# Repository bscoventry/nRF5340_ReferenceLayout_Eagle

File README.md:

# nRF5340 Eagle Reference Layout

This is a recreation of Nordic's reference layout for the nRF5340 in Eagle. The layout given by Nordic is in Altium, and it might be useful to those who do not have access to that software. While it's pin and pcb perfect replication, users should use with caution and validation since I am not Nordic.

# Nordic nRF5340 Circuit Configuration 3.
This is implemented for the reference circuit configuration 3, which has the following configuration parameters:

This can be easily ajdusted to other configurations by minor changes to reference schematic and board layout.

Note: This does require a 4 layer board due to Eagle restrictions on microvias. Will fix this in later iterations.

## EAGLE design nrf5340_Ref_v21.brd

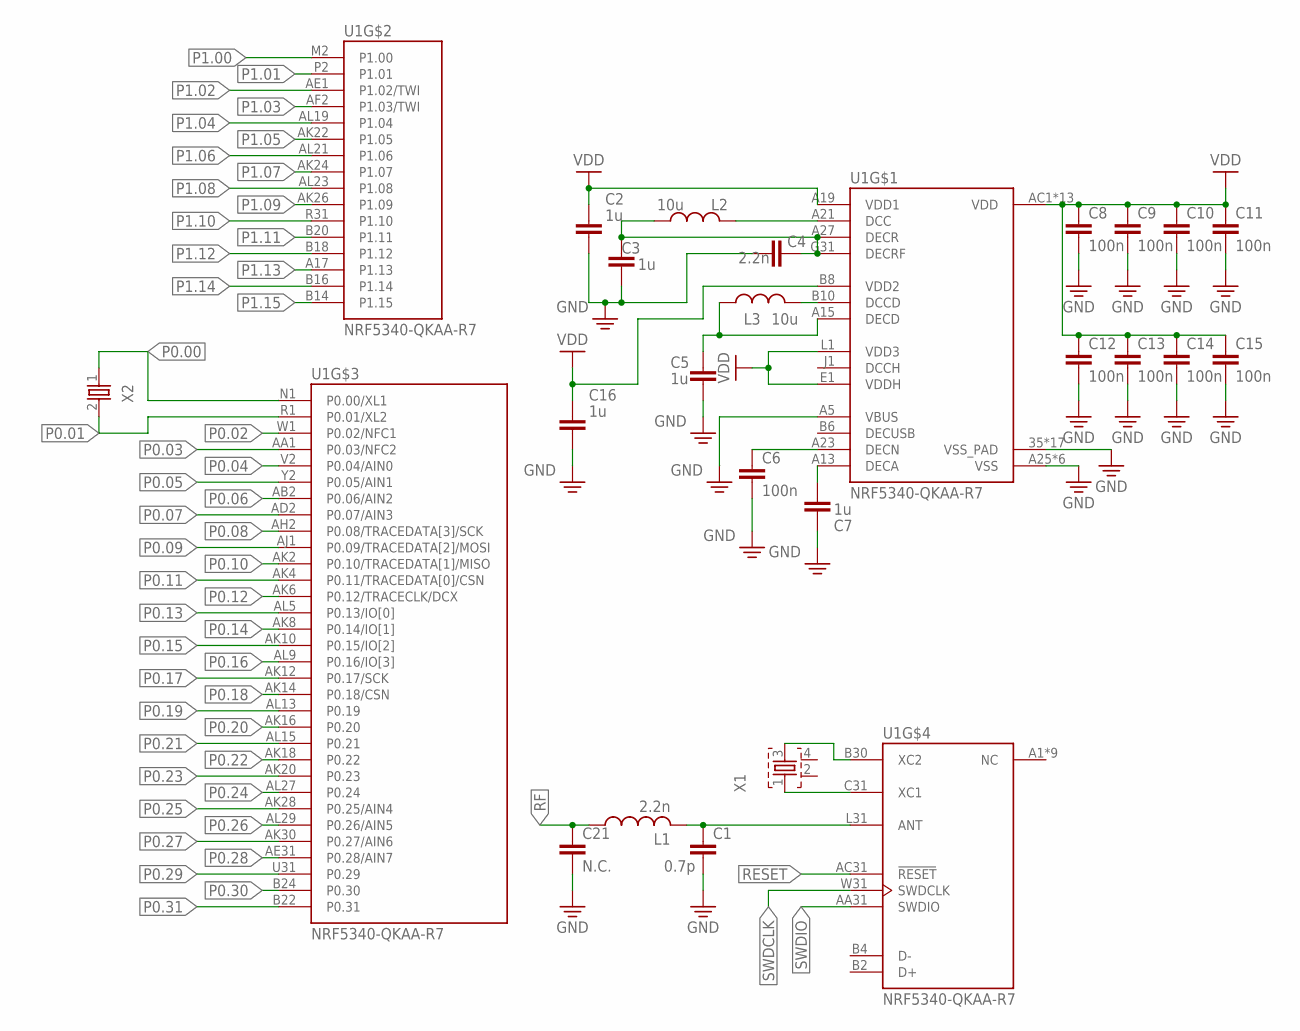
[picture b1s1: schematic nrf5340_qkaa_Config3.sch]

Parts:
C1: 0.7p; RESC0201_N
C2, C3, C5, C7, C16: 1u; CAPC1005X60
C4: 2.2n; RESC0201_N
C6, C8, C9, C10, C11, C12, C13, C14, C15: 100n; RESC0201_N
C21: N.C.; RESC0201_N
L1: 2.2n; RESC0201_N
L2, L3: 10u; INDC1608X95N
U1: NRF5340-QKAA-R7; XCVR_NRF5340-QKAA-R7
X1: XTAL_32MHZ; BT-XTAL_2016_N
X2: XTAL_32KHZ; XTAL_3215_N

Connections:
DCCH: U1.J1 (DCCH)
DECUSB: U1.B6 (DECUSB)
GND: C1.2, C2.2, C3.2, C4.2, C5.2, C6.2, C7.2, C8.2, C9.2, C10.2, C11.2, C12.2, C13.2, C14.2, C15.2, C16.2, C21.2, U1.35 (VSS_PAD), U1.36 (VSS_PAD), U1.37 (VSS_PAD), U1.38 (VSS_PAD), U1.39 (VSS_PAD), U1.40 (VSS_PAD), U1.41 (VSS_PAD), U1.43 (VSS_PAD), U1.44 (VSS_PAD), U1.45 (VSS_PAD), U1.46 (VSS_PAD), U1.47 (VSS_PAD), U1.48 (VSS_PAD), U1.49 (VSS_PAD), U1.50 (VSS_PAD), U1.51 (VSS_PAD), U1.104 (VSS_PAD), U1.A5 (VBUS), U1.A25 (VSS), U1.B12 (VSS), U1.B26 (VSS), U1.G1 (VSS), U1.H2 (VSS), U1.J31 (VSS)
unnamed: C1.1, L1.2, U1.L31 (ANT)
unnamed: U1.C31 (XC1), X1.1
unnamed: U1.B30 (XC2), X1.3
unnamed: C6.1, U1.A23 (DECN)
unnamed: L2.2, U1.A21 (DCC)
unnamed: L3.2, U1.B10 (DCCD)
unnamed: C5.1, L3.1, U1.A15 (DECD)
unnamed: C3.1, C4.1, L2.1, U1.A27 (DECR), U1.G31 (DECRF)
unnamed: C7.1, U1.A13 (DECA)
P0.00: U1.N1 (P0.00/XL1), X2.1
P0.01: U1.R1 (P0.01/XL2), X2.2
P0.02: U1.W1 (P0.02/NFC1)
P0.03: U1.AA1 (P0.03/NFC2)
P0.04: U1.V2 (P0.04/AIN0)
P0.05: U1.Y2 (P0.05/AIN1)
P0.06: U1.AB2 (P0.06/AIN2)
P0.07: U1.AD2 (P0.07/AIN3)
P0.08: U1.AH2 (P0.08/TRACEDATA[3]/SCK)
P0.09: U1.AJ1 (P0.09/TRACEDATA[2]/MOSI)
P0.10: U1.AK2 (P0.10/TRACEDATA[1]/MISO)
P0.11: U1.AK4 (P0.11/TRACEDATA[0]/CSN)
P0.12: U1.AK6 (P0.12/TRACECLK/DCX)
P0.13: U1.AL5 (P0.13/IO[0])
P0.14: U1.AK8 (P0.14/IO[1])
P0.15: U1.AK10 (P0.15/IO[2])
P0.16: U1.AL9 (P0.16/IO[3])
P0.17: U1.AK12 (P0.17/SCK)
P0.18: U1.AK14 (P0.18/CSN)
P0.19: U1.AL13 (P0.19)
P0.20: U1.AK16 (P0.20)
P0.21: U1.AL15 (P0.21)
P0.22: U1.AK18 (P0.22)
P0.23: U1.AK20 (P0.23)
P0.24: U1.AL27 (P0.24)
P0.25: U1.AK28 (P0.25/AIN4)
P0.26: U1.AL29 (P0.26/AIN5)
P0.27: U1.AK30 (P0.27/AIN6)
P0.28: U1.AE31 (P0.28/AIN7)
P0.29: U1.U31 (P0.29)
P0.30: U1.B24 (P0.30)
P0.31: U1.B22 (P0.31)
P1.00: U1.M2 (P1.00)
P1.01: U1.P2 (P1.01)
P1.02: U1.AE1 (P1.02/TWI)
P1.03: U1.AF2 (P1.03/TWI)
P1.04: U1.AL19 (P1.04)
P1.05: U1.AK22 (P1.05)
P1.06: U1.AL21 (P1.06)
P1.07: U1.AK24 (P1.07)
P1.08: U1.AL23 (P1.08)
P1.09: U1.AK26 (P1.09)
P1.10: U1.R31 (P1.10)
P1.11: U1.B20 (P1.11)
P1.12: U1.B18 (P1.12)
P1.13: U1.A17 (P1.13)
P1.14: U1.B16 (P1.14)
P1.15: U1.B14 (P1.15)
RESET: U1.AC31 (!RESET)
RF: C21.1, L1.1
SWDCLK: U1.W31 (SWDCLK)
SWDIO: U1.AA31 (SWDIO)
VDD: C2.1, C8.1, C9.1, C10.1, C11.1, C12.1, C13.1, C14.1, C15.1, C16.1, U1.A19 (VDD1), U1.AC1 (VDD), U1.AG1 (VDD), U1.AJ31 (VDD), U1.AL3 (VDD), U1.AL7 (VDD), U1.AL11 (VDD), U1.AL17 (VDD), U1.AL25 (VDD), U1.B8 (VDD2), U1.B28 (VDD), U1.C1 (VDD), U1.E1 (VDDH), U1.E31 (VDD), U1.L1 (VDD3), U1.N31 (VDD), U1.U1 (VDD)

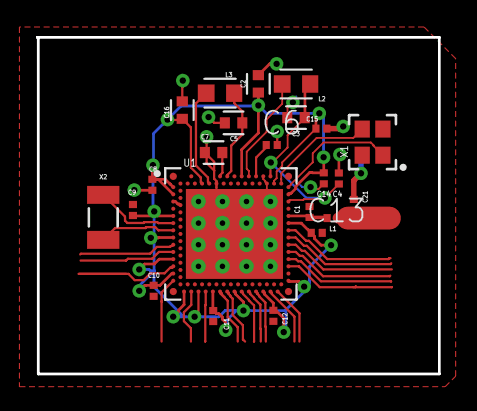
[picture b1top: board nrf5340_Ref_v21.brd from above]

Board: 4 copper layers, 22.3 x 18.7 mm, 23 parts (0 on the bottom side), 14 nets.

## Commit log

2025-02-04 Added Ref Schematic
2025-02-04 Added reference figure table
2025-02-05 Added Board
2025-02-05 Fixed nRF Blind Via Problem
2025-02-05 Added Layout Image
2025-03-08 Updated Layout Image
2025-03-08 Updated schematic
2025-03-08 Updated Board
2025-03-08 Added updated layout
